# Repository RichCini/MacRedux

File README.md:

# MacRedux

Reimaging of the original Macintosh 128k logic board 820-0086-C. 

## Introduction
This project is a re-implementation of a Macintosh 128k logic board. From this, I hope to
derive the 128k/512k hybrid board. Primarily, I expect these would be used to replace
an original logic board that has been damaged. There are several components that are generally 
"unobtanium" without harvesting from another board. These parts include the six PLDs (of which 
only 2 or 3 may have been decoded per some Google searching), the IWM (disk drive controller), 
the RTC chip (although a clone seems to have been made by someone), three RC dampers, and the 
external floppy connector (a custom 19-pin connector that looks like it used the DB13W3 shell
size). The DB19F was also used on the //gs, Amiga, and NeXT machines, among others. You can 
still occasionally find them on eBay. I purchased 2 just to have them for measurements.

## Project Status
The board has been fully test plotted but has not been sent to manufacturing. I was able to
purchase an original board, so most of the critical measurements have been validated. However,
there still may be minor differences between the original and this version, mostly relating to
the rear connectors, the RJ11 jack, and the pushbutton switches on the side. 

## Versions
* v1.0-001: Initial prototype based on original schematic.

## Known Bugs/Issues
* The board still contains several DRC errors, mostly due to components encroaching on
eachother ("porch violations"). There will likely be permanent encroachments given how
dense the board is in certain areas.

* Certain components (like the push buttons, keyboard connector, and audio jack) 
are being replaced with what I think are current equivalents, so further adjustments could
be needed for those so that they are positioned properly on the planar.

* As of now, the PALs have not been fully decoded. The archive includes a text
file with some notes I've collected on the topic from various places on the Net.

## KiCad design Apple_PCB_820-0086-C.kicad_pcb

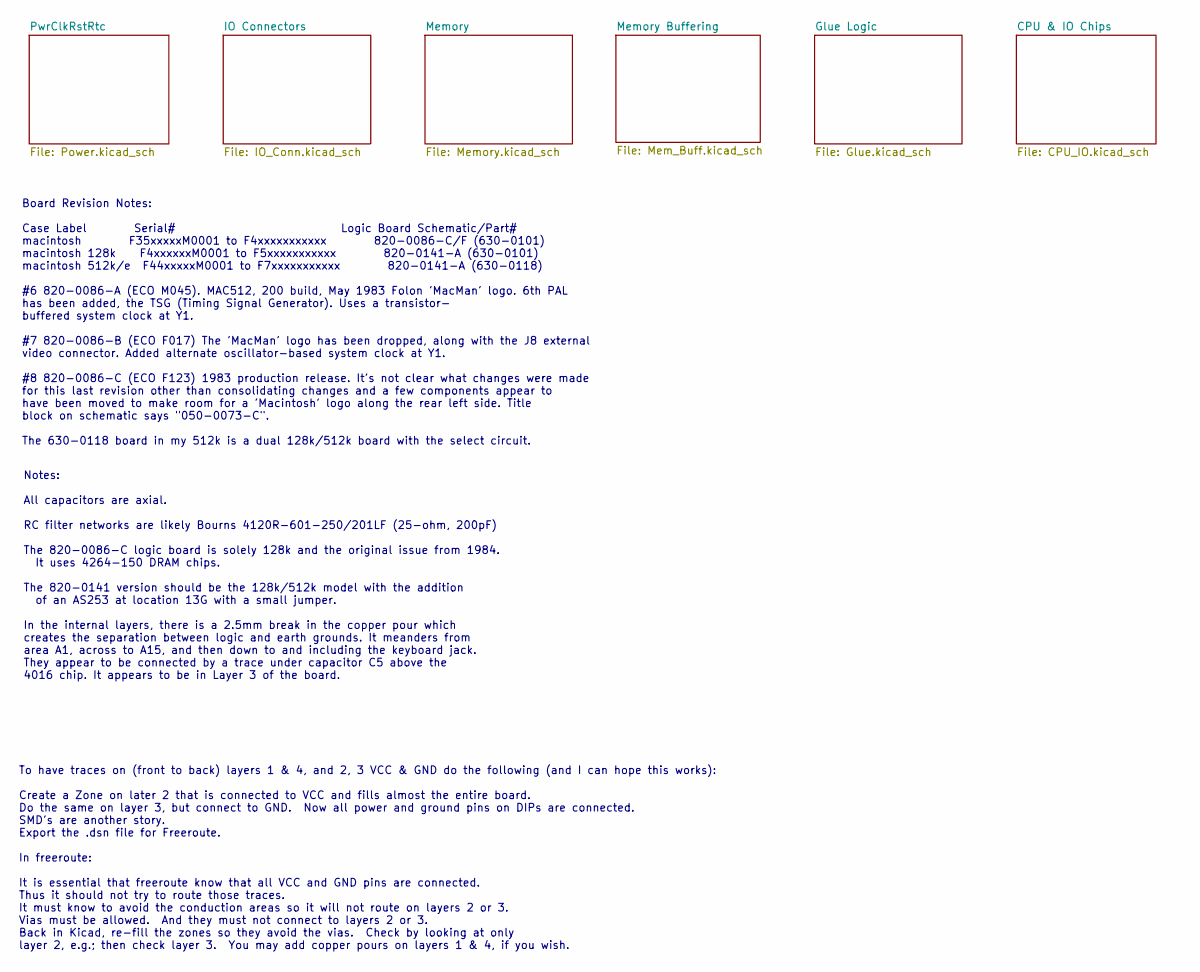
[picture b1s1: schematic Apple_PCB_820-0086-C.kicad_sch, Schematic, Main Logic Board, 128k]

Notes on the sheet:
Board Revision Notes: Case Label Serial# Logic Board Schematic/Part# macintosh F35xxxxxM0001 to F4xxxxxxxxxxx 820-0086-C/F (630-0101) macintosh 128k F4xxxxxxM0001 to F5xxxxxxxxxxx 820-0141-A (630-0101) macintosh 512k/e F44xxxxxM0001 to F7xxxxxxxxxxx 820-0141-A (630-0118) #6 820-0086-A (ECO M045). M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
To have traces on (front to back) layers 1 & 4, and 2, 3 VCC & GND do the following (and I can hope this works): Create a Zone on later 2 that is connected to VCC and fills almost the entire board. Do the same on layer 3, but connect to GND. Now all power and ground pins on DIPs are connected. SMD'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
Notes: All capacitors are axial. RC filter networks are likely Bourns 4120R-601-250/201LF (25-ohm, 200pF) The 820-0086-C logic board is solely 128k and the original issue from 1984. It uses 4264-150 DRAM chips. The 820-0141 version should be the 128k/512k model with the addition of an AS253 at loca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

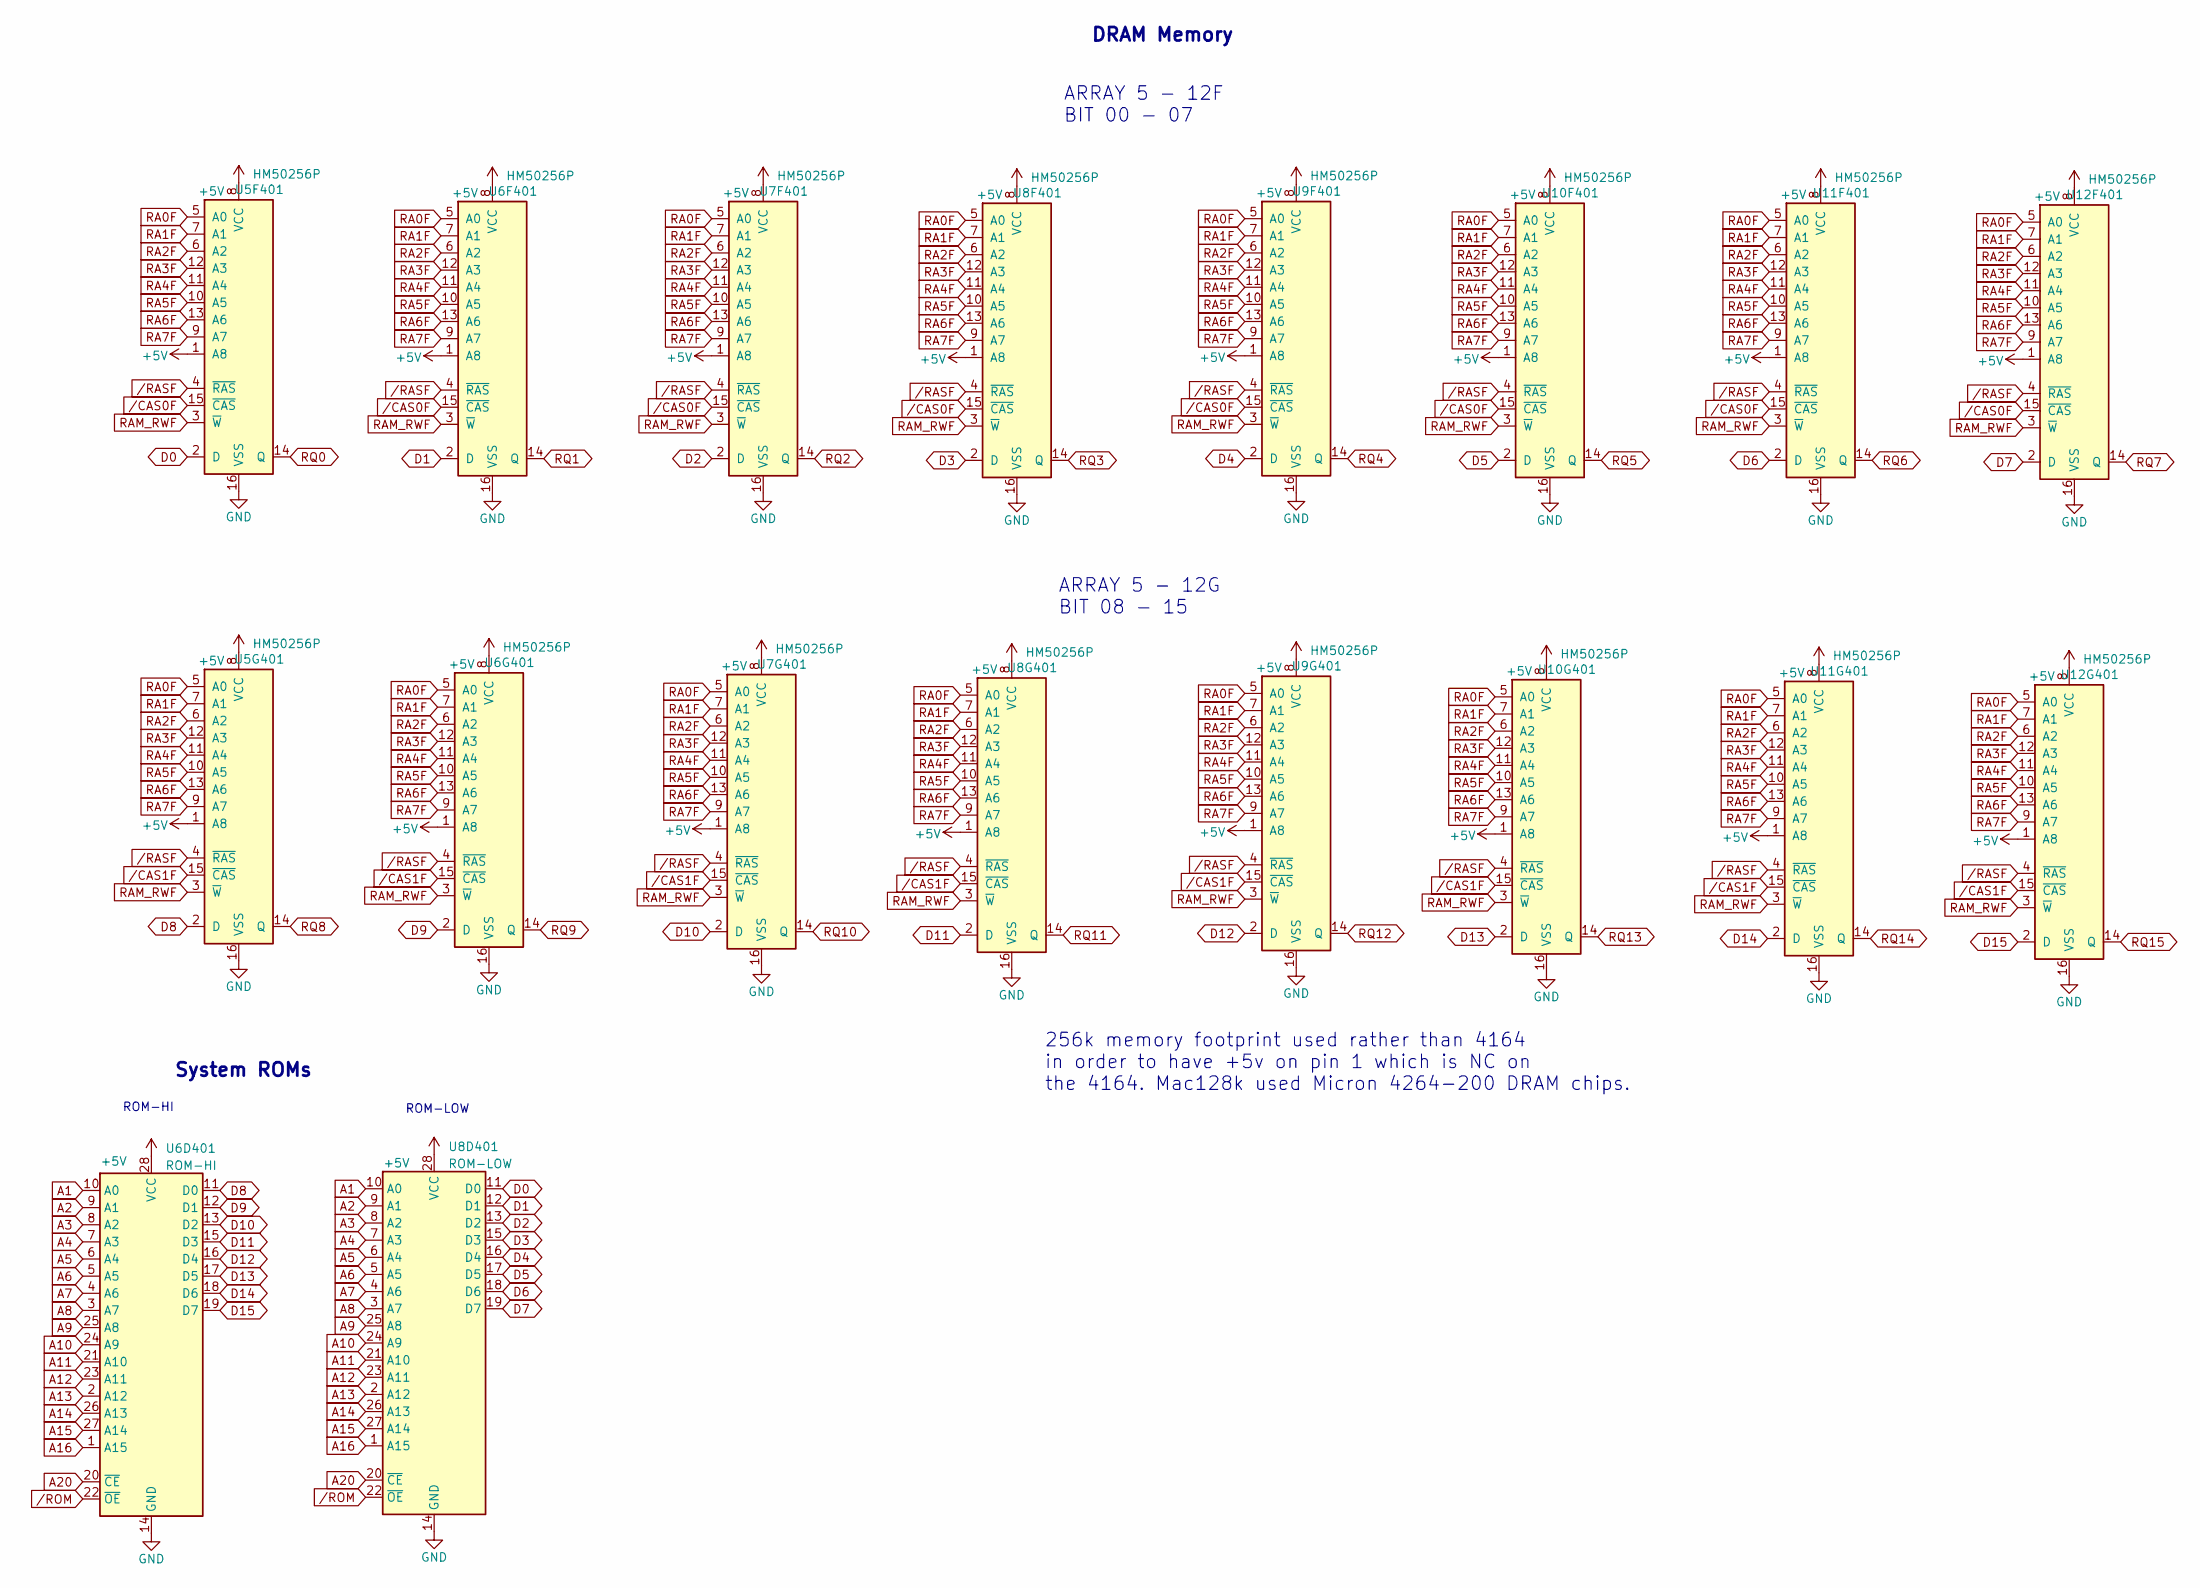
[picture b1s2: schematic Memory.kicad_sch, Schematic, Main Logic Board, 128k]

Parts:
U5F401, U5G401, U6F401, U6G401, U7F401, U7G401, U8F401, U8G401, U9F401, U9G401, U10F401, U10G401, U11F401, U11G401, U12F401, U12G401: HM50256P; DIP-16_W7.62mm_Socket_LongPads
U6D401: ROM-HI; DIP-28_W15.24mm_LongPads
U8D401: ROM-LOW; DIP-28_W15.24mm_LongPads

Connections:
+5V: U5F401.1 (A8), U5F401.8 (VCC), U5G401.1 (A8), U5G401.8 (VCC), U6D401.28 (VCC), U6F401.1 (A8), U6F401.8 (VCC), U6G401.1 (A8), U6G401.8 (VCC), U7F401.1 (A8), U7F401.8 (VCC), U7G401.1 (A8), U7G401.8 (VCC), U8D401.28 (VCC), U8F401.1 (A8), U8F401.8 (VCC), U8G401.1 (A8), U8G401.8 (VCC), U9F401.1 (A8), U9F401.8 (VCC), U9G401.1 (A8), U9G401.8 (VCC), U10F401.1 (A8), U10F401.8 (VCC), U10G401.1 (A8), U10G401.8 (VCC), U11F401.1 (A8), U11F401.8 (VCC), U11G401.1 (A8), U11G401.8 (VCC), U12F401.1 (A8), U12F401.8 (VCC), U12G401.1 (A8), U12G401.8 (VCC); also elsewhere on the board
A1: U6D401.10 (A0), U8D401.10 (A0); also elsewhere on the board
A2: U6D401.9 (A1), U8D401.9 (A1); also elsewhere on the board
A3: U6D401.8 (A2), U8D401.8 (A2); also elsewhere on the board
A4: U6D401.7 (A3), U8D401.7 (A3); also elsewhere on the board
A5: U6D401.6 (A4), U8D401.6 (A4); also elsewhere on the board
A6: U6D401.5 (A5), U8D401.5 (A5); also elsewhere on the board
A7: U6D401.4 (A6), U8D401.4 (A6); also elsewhere on the board
A8: U6D401.3 (A7), U8D401.3 (A7); also elsewhere on the board
A9: U6D401.25 (A8), U8D401.25 (A8); also elsewhere on the board
A10: U6D401.24 (A9), U8D401.24 (A9); also elsewhere on the board
A11: U6D401.21 (A10), U8D401.21 (A10); also elsewhere on the board
A12: U6D401.23 (A11), U8D401.23 (A11); also elsewhere on the board
A13: U6D401.2 (A12), U8D401.2 (A12); also elsewhere on the board
A14: U6D401.26 (A13), U8D401.26 (A13); also elsewhere on the board
A15: U6D401.27 (A14), U8D401.27 (A14); also elsewhere on the board
A16: U6D401.1 (A15), U8D401.1 (A15); also elsewhere on the board
A20: U6D401.20 (~CE), U8D401.20 (~CE); also elsewhere on the board
D0: U5F401.2 (D), U8D401.11 (D0); also elsewhere on the board
D1: U6F401.2 (D), U8D401.12 (D1); also elsewhere on the board
D2: U7F401.2 (D), U8D401.13 (D2); also elsewhere on the board
D3: U8D401.15 (D3), U8F401.2 (D); also elsewhere on the board
D4: U8D401.16 (D4), U9F401.2 (D); also elsewhere on the board
D5: U8D401.17 (D5), U10F401.2 (D); also elsewhere on the board
D6: U8D401.18 (D6), U11F401.2 (D); also elsewhere on the board
D7: U8D401.19 (D7), U12F401.2 (D); also elsewhere on the board
D8: U5G401.2 (D), U6D401.11 (D0); also elsewhere on the board
D9: U6D401.12 (D1), U6G401.2 (D); also elsewhere on the board
D10: U6D401.13 (D2), U7G401.2 (D); also elsewhere on the board
D11: U6D401.15 (D3), U8G401.2 (D); also elsewhere on the board
D12: U6D401.16 (D4), U9G401.2 (D); also elsewhere on the board
D13: U6D401.17 (D5), U10G401.2 (D); also elsewhere on the board
D14: U6D401.18 (D6), U11G401.2 (D); also elsewhere on the board
D15: U6D401.19 (D7), U12G401.2 (D); also elsewhere on the board
GND: U5F401.16 (VSS), U5G401.16 (VSS), U6D401.14 (GND), U6F401.16 (VSS), U6G401.16 (VSS), U7F401.16 (VSS), U7G401.16 (VSS), U8D401.14 (GND), U8F401.16 (VSS), U8G401.16 (VSS), U9F401.16 (VSS), U9G401.16 (VSS), U10F401.16 (VSS), U10G401.16 (VSS), U11F401.16 (VSS), U11G401.16 (VSS), U12F401.16 (VSS), U12G401.16 (VSS); also elsewhere on the board
RA0F: U5F401.5 (A0), U5G401.5 (A0), U6F401.5 (A0), U6G401.5 (A0), U7F401.5 (A0), U7G401.5 (A0), U8F401.5 (A0), U8G401.5 (A0), U9F401.5 (A0), U9G401.5 (A0), U10F401.5 (A0), U10G401.5 (A0), U11F401.5 (A0), U11G401.5 (A0), U12F401.5 (A0), U12G401.5 (A0); also elsewhere on the board
RA1F: U5F401.7 (A1), U5G401.7 (A1), U6F401.7 (A1), U6G401.7 (A1), U7F401.7 (A1), U7G401.7 (A1), U8F401.7 (A1), U8G401.7 (A1), U9F401.7 (A1), U9G401.7 (A1), U10F401.7 (A1), U10G401.7 (A1), U11F401.7 (A1), U11G401.7 (A1), U12F401.7 (A1), U12G401.7 (A1); also elsewhere on the board
RA2F: U5F401.6 (A2), U5G401.6 (A2), U6F401.6 (A2), U6G401.6 (A2), U7F401.6 (A2), U7G401.6 (A2), U8F401.6 (A2), U8G401.6 (A2), U9F401.6 (A2), U9G401.6 (A2), U10F401.6 (A2), U10G401.6 (A2), U11F401.6 (A2), U11G401.6 (A2), U12F401.6 (A2), U12G401.6 (A2); also elsewhere on the board
RA3F: U5F401.12 (A3), U5G401.12 (A3), U6F401.12 (A3), U6G401.12 (A3), U7F401.12 (A3), U7G401.12 (A3), U8F401.12 (A3), U8G401.12 (A3), U9F401.12 (A3), U9G401.12 (A3), U10F401.12 (A3), U10G401.12 (A3), U11F401.12 (A3), U11G401.12 (A3), U12F401.12 (A3), U12G401.12 (A3); also elsewhere on the board
RA4F: U5F401.11 (A4), U5G401.11 (A4), U6F401.11 (A4), U6G401.11 (A4), U7F401.11 (A4), U7G401.11 (A4), U8F401.11 (A4), U8G401.11 (A4), U9F401.11 (A4), U9G401.11 (A4), U10F401.11 (A4), U10G401.11 (A4), U11F401.11 (A4), U11G401.11 (A4), U12F401.11 (A4), U12G401.11 (A4); also elsewhere on the board
RA5F: U5F401.10 (A5), U5G401.10 (A5), U6F401.10 (A5), U6G401.10 (A5), U7F401.10 (A5), U7G401.10 (A5), U8F401.10 (A5), U8G401.10 (A5), U9F401.10 (A5), U9G401.10 (A5), U10F401.10 (A5), U10G401.10 (A5), U11F401.10 (A5), U11G401.10 (A5), U12F401.10 (A5), U12G401.10 (A5); also elsewhere on the board
RA6F: U5F401.13 (A6), U5G401.13 (A6), U6F401.13 (A6), U6G401.13 (A6), U7F401.13 (A6), U7G401.13 (A6), U8F401.13 (A6), U8G401.13 (A6), U9F401.13 (A6), U9G401.13 (A6), U10F401.13 (A6), U10G401.13 (A6), U11F401.13 (A6), U11G401.13 (A6), U12F401.13 (A6), U12G401.13 (A6); also elsewhere on the board
RA7F: U5F401.9 (A7), U5G401.9 (A7), U6F401.9 (A7), U6G401.9 (A7), U7F401.9 (A7), U7G401.9 (A7), U8F401.9 (A7), U8G401.9 (A7), U9F401.9 (A7), U9G401.9 (A7), U10F401.9 (A7), U10G401.9 (A7), U11F401.9 (A7), U11G401.9 (A7), U12F401.9 (A7), U12G401.9 (A7); also elsewhere on the board
RAM_RWF: U5F401.3 (~W), U5G401.3 (~W), U6F401.3 (~W), U6G401.3 (~W), U7F401.3 (~W), U7G401.3 (~W), U8F401.3 (~W), U8G401.3 (~W), U9F401.3 (~W), U9G401.3 (~W), U10F401.3 (~W), U10G401.3 (~W), U11F401.3 (~W), U11G401.3 (~W), U12F401.3 (~W), U12G401.3 (~W); also elsewhere on the board
RQ0: U5F401.14 (Q); also elsewhere on the board
RQ1: U6F401.14 (Q); also elsewhere on the board
RQ2: U7F401.14 (Q); also elsewhere on the board
RQ3: U8F401.14 (Q); also elsewhere on the board
RQ4: U9F401.14 (Q); also elsewhere on the board
RQ5: U10F401.14 (Q); also elsewhere on the board
RQ6: U11F401.14 (Q); also elsewhere on the board
RQ7: U12F401.14 (Q); also elsewhere on the board
RQ8: U5G401.14 (Q); also elsewhere on the board
RQ9: U6G401.14 (Q); also elsewhere on the board
RQ10: U7G401.14 (Q); also elsewhere on the board
RQ11: U8G401.14 (Q); also elsewhere on the board
RQ12: U9G401.14 (Q); also elsewhere on the board
RQ13: U10G401.14 (Q); also elsewhere on the board
RQ14: U11G401.14 (Q); also elsewhere on the board
RQ15: U12G401.14 (Q); also elsewhere on the board
/CAS0F: U5F401.15 (~CAS), U6F401.15 (~CAS), U7F401.15 (~CAS), U8F401.15 (~CAS), U9F401.15 (~CAS), U10F401.15 (~CAS), U11F401.15 (~CAS), U12F401.15 (~CAS); also elsewhere on the board
/CAS1F: U5G401.15 (~CAS), U6G401.15 (~CAS), U7G401.15 (~CAS), U8G401.15 (~CAS), U9G401.15 (~CAS), U10G401.15 (~CAS), U11G401.15 (~CAS), U12G401.15 (~CAS); also elsewhere on the board
/RASF: U5F401.4 (~RAS), U5G401.4 (~RAS), U6F401.4 (~RAS), U6G401.4 (~RAS), U7F401.4 (~RAS), U7G401.4 (~RAS), U8F401.4 (~RAS), U8G401.4 (~RAS), U9F401.4 (~RAS), U9G401.4 (~RAS), U10F401.4 (~RAS), U10G401.4 (~RAS), U11F401.4 (~RAS), U11G401.4 (~RAS), U12F401.4 (~RAS), U12G401.4 (~RAS); also elsewhere on the board
/ROM: U6D401.22 (~OE), U8D401.22 (~OE); also elsewhere on the board

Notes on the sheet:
ARRAY 5 - 12F BIT 00 - 07
ROM-LOW
DRAM Memory
System ROMs
ARRAY 5 - 12G BIT 08 - 15
ROM-HI
256k memory footprint used rather than 4164 in order to have +5v on pin 1 which is NC on the 4164. Mac128k used Micron 4264-200 DRAM chips.

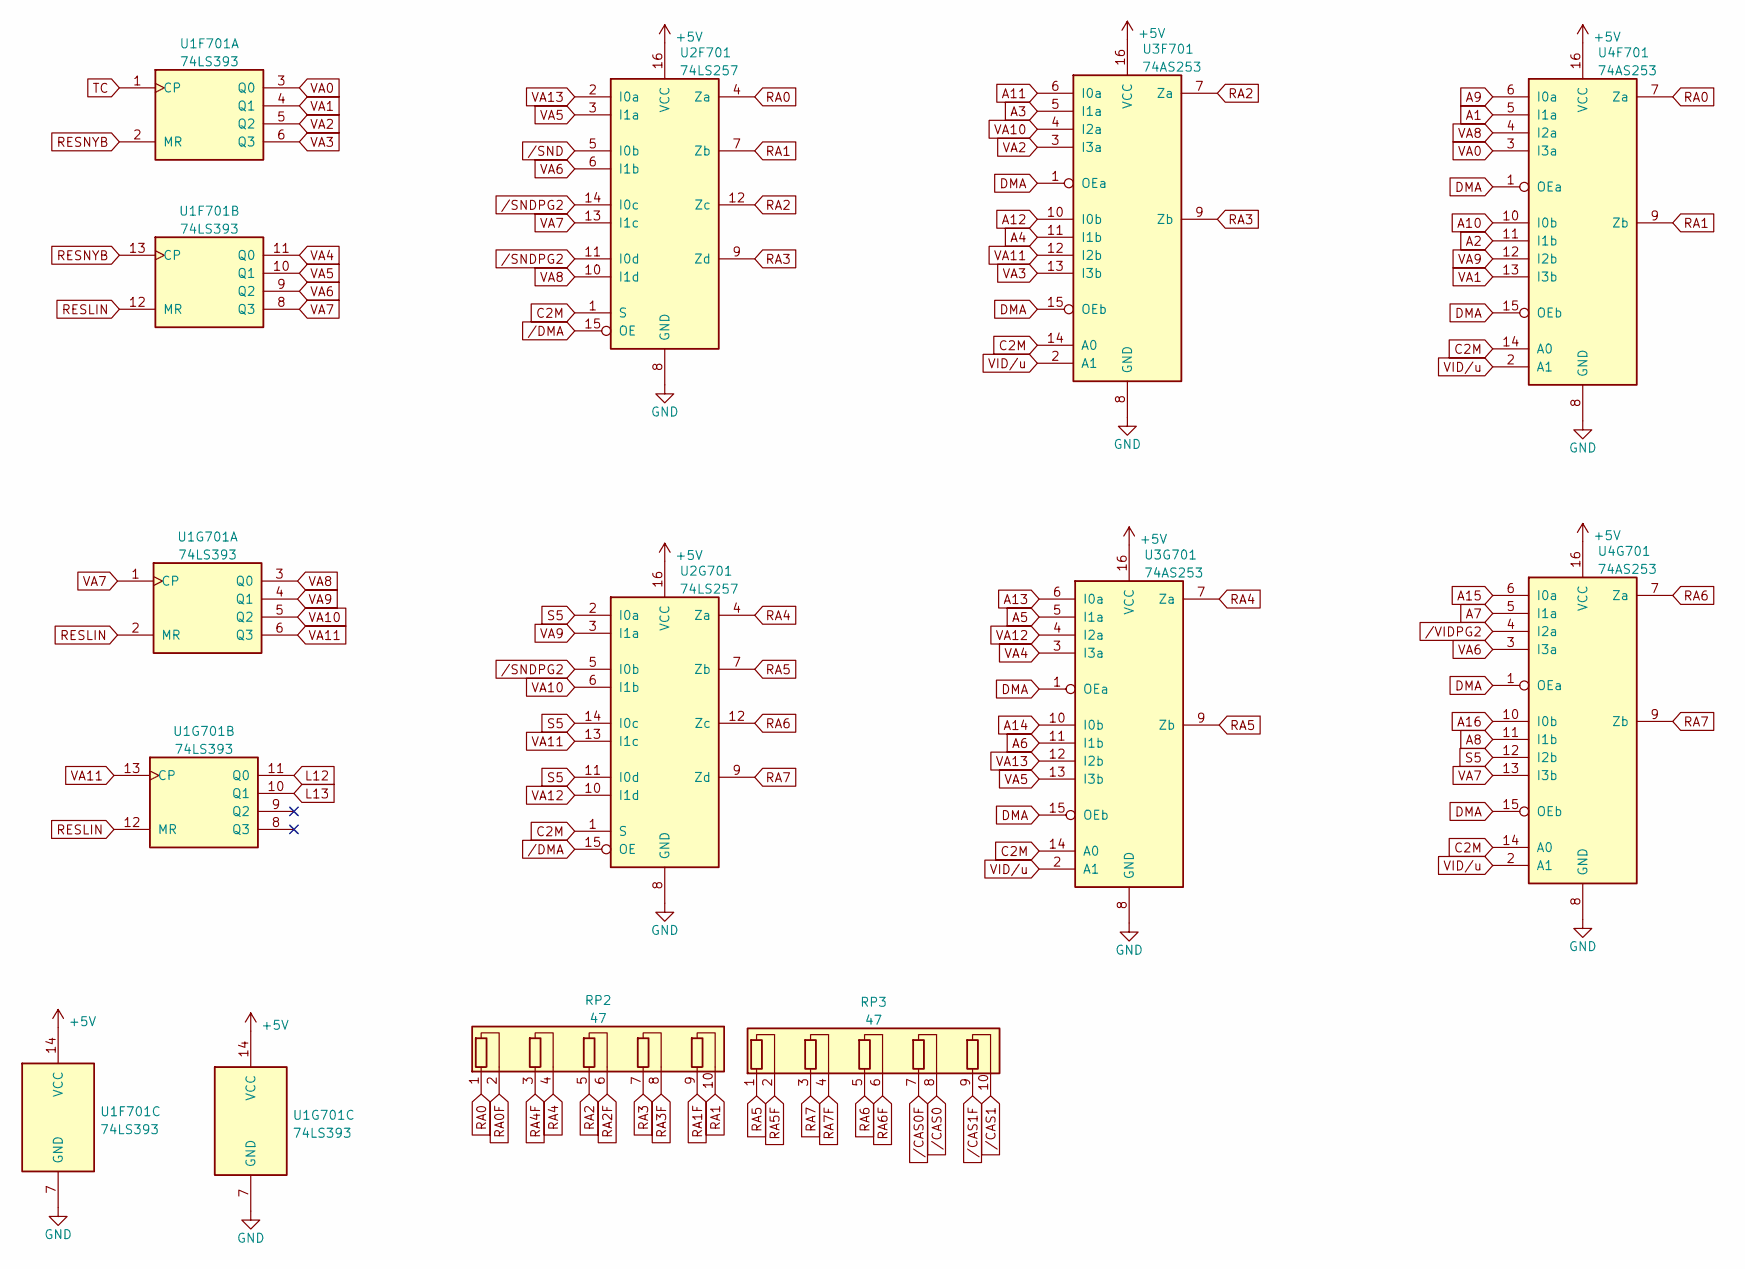
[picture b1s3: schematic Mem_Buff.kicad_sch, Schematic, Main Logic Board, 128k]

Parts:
RP2, RP3: 47; R_Array_SIP10
U1F701, U1G701: 74LS393; DIP-14_W7.62mm_Socket_LongPads
U2F701, U2G701: 74LS257; DIP-16_W7.62mm_Socket_LongPads
U3F701, U3G701, U4F701, U4G701: 74AS253; DIP-16_W7.62mm_Socket_LongPads

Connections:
+5V: U1F701.14 (VCC), U1G701.14 (VCC), U2F701.16 (VCC), U2G701.16 (VCC), U3F701.16 (VCC), U3G701.16 (VCC), U4F701.16 (VCC), U4G701.16 (VCC); also elsewhere on the board
A1: U4F701.5 (I1a); also elsewhere on the board
A2: U4F701.11 (I1b); also elsewhere on the board
A3: U3F701.5 (I1a); also elsewhere on the board
A4: U3F701.11 (I1b); also elsewhere on the board
A5: U3G701.5 (I1a); also elsewhere on the board
A6: U3G701.11 (I1b); also elsewhere on the board
A7: U4G701.5 (I1a); also elsewhere on the board
A8: U4G701.11 (I1b); also elsewhere on the board
A9: U4F701.6 (I0a); also elsewhere on the board
A10: U4F701.10 (I0b); also elsewhere on the board
A11: U3F701.6 (I0a); also elsewhere on the board
A12: U3F701.10 (I0b); also elsewhere on the board
A13: U3G701.6 (I0a); also elsewhere on the board
A14: U3G701.10 (I0b); also elsewhere on the board
A15: U4G701.6 (I0a); also elsewhere on the board
A16: U4G701.10 (I0b); also elsewhere on the board
C2M: U2F701.1 (S), U2G701.1 (S), U3F701.14 (A0), U3G701.14 (A0), U4F701.14 (A0), U4G701.14 (A0); also elsewhere on the board
DMA: U3F701.1 (OEa), U3F701.15 (OEb), U3G701.1 (OEa), U3G701.15 (OEb), U4F701.1 (OEa), U4F701.15 (OEb), U4G701.1 (OEa), U4G701.15 (OEb); also elsewhere on the board
GND: U1F701.7 (GND), U1G701.7 (GND), U2F701.8 (GND), U2G701.8 (GND), U3F701.8 (GND), U3G701.8 (GND), U4F701.8 (GND), U4G701.8 (GND); also elsewhere on the board
L12: U1G701.11 (Q0); also elsewhere on the board
L13: U1G701.10 (Q1); also elsewhere on the board
RA0: RP2.1 (R1.1), U2F701.4 (Za), U4F701.7 (Za)
RA0F: RP2.2 (R1.2); also elsewhere on the board
RA1: RP2.10 (R5.2), U2F701.7 (Zb), U4F701.9 (Zb)
RA1F: RP2.9 (R5.1); also elsewhere on the board
RA2: RP2.5 (R3.1), U2F701.12 (Zc), U3F701.7 (Za)
RA2F: RP2.6 (R3.2); also elsewhere on the board
RA3: RP2.7 (R4.1), U2F701.9 (Zd), U3F701.9 (Zb)
RA3F: RP2.8 (R4.2); also elsewhere on the board
RA4: RP2.4 (R2.2), U2G701.4 (Za), U3G701.7 (Za)
RA4F: RP2.3 (R2.1); also elsewhere on the board
RA5: RP3.1 (R1.1), U2G701.7 (Zb), U3G701.9 (Zb)
RA5F: RP3.2 (R1.2); also elsewhere on the board
RA6: RP3.5 (R3.1), U2G701.12 (Zc), U4G701.7 (Za)
RA6F: RP3.6 (R3.2); also elsewhere on the board
RA7: RP3.3 (R2.1), U2G701.9 (Zd), U4G701.9 (Zb)
RA7F: RP3.4 (R2.2); also elsewhere on the board
RESLIN: U1F701.12 (MR), U1G701.2 (MR), U1G701.12 (MR); also elsewhere on the board
RESNYB: U1F701.2 (MR), U1F701.13 (CP); also elsewhere on the board
S5: U2G701.2 (I0a), U2G701.11 (I0d), U2G701.14 (I0c), U4G701.12 (I2b); also elsewhere on the board
TC: U1F701.1 (CP); also elsewhere on the board
VA0: U1F701.3 (Q0), U4F701.3 (I3a); also elsewhere on the board
VA1: U1F701.4 (Q1), U4F701.13 (I3b); also elsewhere on the board
VA2: U1F701.5 (Q2), U3F701.3 (I3a); also elsewhere on the board
VA3: U1F701.6 (Q3), U3F701.13 (I3b); also elsewhere on the board
VA4: U1F701.11 (Q0), U3G701.3 (I3a)
VA5: U1F701.10 (Q1), U2F701.3 (I1a), U3G701.13 (I3b)
VA6: U1F701.9 (Q2), U2F701.6 (I1b), U4G701.3 (I3a); also elsewhere on the board
VA7: U1F701.8 (Q3), U1G701.1 (CP), U2F701.13 (I1c), U4G701.13 (I3b); also elsewhere on the board
VA8: U1G701.3 (Q0), U2F701.10 (I1d), U4F701.4 (I2a); also elsewhere on the board
VA9: U1G701.4 (Q1), U2G701.3 (I1a), U4F701.12 (I2b); also elsewhere on the board
VA10: U1G701.5 (Q2), U2G701.6 (I1b), U3F701.4 (I2a); also elsewhere on the board
VA11: U1G701.6 (Q3), U1G701.13 (CP), U2G701.13 (I1c), U3F701.12 (I2b); also elsewhere on the board
VA12: U2G701.10 (I1d), U3G701.4 (I2a); also elsewhere on the board
VA13: U2F701.2 (I0a), U3G701.12 (I2b); also elsewhere on the board
VID/u: U3F701.2 (A1), U3G701.2 (A1), U4F701.2 (A1), U4G701.2 (A1); also elsewhere on the board
/CAS0: RP3.8 (R4.2); also elsewhere on the board
/CAS0F: RP3.7 (R4.1); also elsewhere on the board
/CAS1: RP3.10 (R5.2); also elsewhere on the board
/CAS1F: RP3.9 (R5.1); also elsewhere on the board
/DMA: U2F701.15 (OE), U2G701.15 (OE); also elsewhere on the board
/SND: U2F701.5 (I0b); also elsewhere on the board
/SNDPG2: U2F701.11 (I0d), U2F701.14 (I0c), U2G701.5 (I0b); also elsewhere on the board
/VIDPG2: U4G701.4 (I2a); also elsewhere on the board

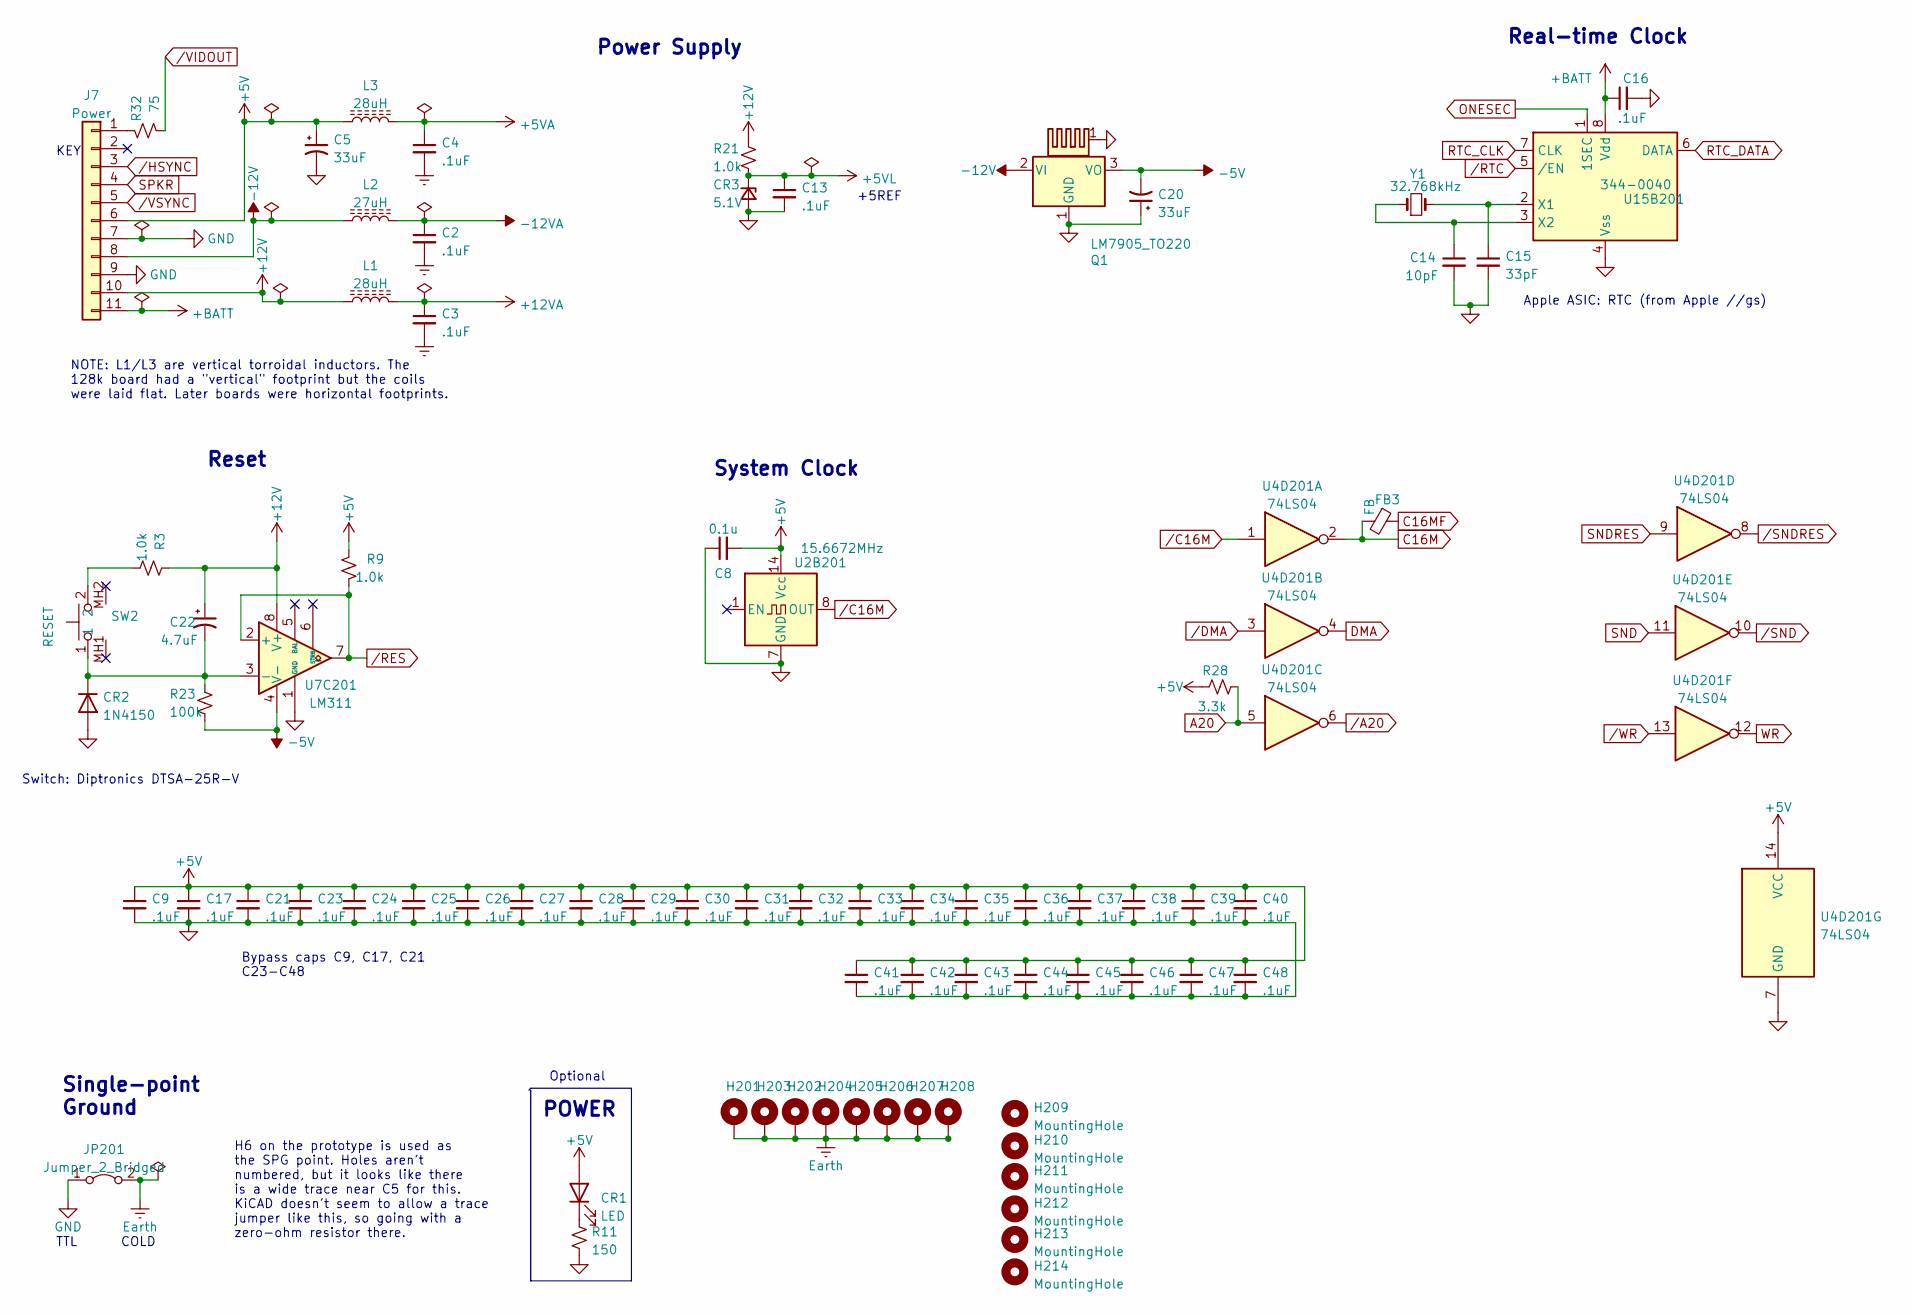
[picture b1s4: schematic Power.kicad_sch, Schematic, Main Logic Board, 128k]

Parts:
C2, C3, C4, C9, C13, C16, C17, C23, C24, C25, C26, C27, C28, C29, C30, C31, C32, C33, C34, C35, C36, C37, C38, C39, C40, C41, C42, C43, C44, C45, C46, C47, C48: .1uF; C_Axial_L3.8mm_D2.6mm_P7.50mm_Horizontal
C5, C20: 33uF; CP_Axial_L11.0mm_D6.0mm_P18.00mm_Horizontal
C8: 0.1u; C_Axial_L3.8mm_D2.6mm_P7.50mm_Horizontal
C14: 10pF; C_Axial_L3.8mm_D2.6mm_P7.50mm_Horizontal
C15: 33pF; C_Axial_L3.8mm_D2.6mm_P7.50mm_Horizontal
C21: .1uF; C_Axial_L5.1mm_D3.1mm_P10.00mm_Horizontal
C22: 4.7uF; CP_Axial_L11.0mm_D5.0mm_P18.00mm_Horizontal
CR1: LED; LED_D5.0mm
CR2: 1N4150; D_DO-35_SOD27_P7.62mm_Horizontal
CR3: 5.1V; D_DO-35_SOD27_P7.62mm_Horizontal
FB3: FB; L_Axial_L7.0mm_D3.3mm_P10.16mm_Horizontal_Fastron_MICC
H201, H202, H203, H204, H205, H206, H207, H208: MountingHole_Pad; MountingHole_2.7mm_M2.5_Pad
H209, H210, H211, H212, H213, H214: MountingHole; MountingHole_2.7mm_M2.5
J7: Power; Molex_KK-396_A-41791-0011_1x11_P3.96mm_Vertical
JP201: Jumper_2_Bridged; TestPoint_Bridge_Pitch5.08mm_Drill0.7mm
L1, L3: 28uH; L_Toroid_Vertical_L14.0mm_W5.6mm_P5.30mm_Bourns_5700
L2: 27uH; L_Axial_L7.0mm_D3.3mm_P10.16mm_Horizontal_Fastron_MICC
Q1: LM7905_TO220; TO-220-3_Horizontal_TabDown_HS
R3, R9, R21: 1.0k; R_Axial_DIN0207_L6.3mm_D2.5mm_P7.62mm_Horizontal
R11: 150; R_Axial_DIN0207_L6.3mm_D2.5mm_P7.62mm_Horizontal
R23: 100k; R_Axial_DIN0207_L6.3mm_D2.5mm_P7.62mm_Horizontal
R28: 3.3k; R_Axial_DIN0207_L6.3mm_D2.5mm_P7.62mm_Horizontal
R32: 75; R_Axial_DIN0207_L6.3mm_D2.5mm_P7.62mm_Horizontal
SW2: RESET; TL1100CF160Q
U2B201: 15.6672MHz; Oscillator_DIP-14
U4D201: 74LS04; DIP-14_W7.62mm_Socket_LongPads
U7C201: LM311; DIP-8_W7.62mm_Socket_LongPads
U15B201: 344-0040; DIP-8_W7.62mm_Socket_LongPads
Y1: 32.768kHz; Crystal_C26-LF_D2.1mm_L6.5mm_Horizontal

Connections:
+5V: C5.1, C8.2, C9.1, C17.1, C21.1, C23.1, C24.1, C25.1, C26.1, C27.1, C28.1, C29.1, C30.1, C31.1, C32.1, C33.1, C34.1, C35.1, C36.1, C37.1, C38.1, C39.1, C40.1, C41.1, C42.1, C43.1, C44.1, C45.1, C46.1, C47.1, C48.1, CR1.2 (A), J7.6, L3.1, R9.1, R28.1, U2B201.14 (Vcc), U4D201.14 (VCC); also elsewhere on the board
+5VA: C4.1, L3.2; also elsewhere on the board
+5VL: C13.1, CR3.1 (K), R21.2; also elsewhere on the board
+12V: C22.1, J7.10, L1.1, R3.1, R21.1, U7C201.8 (V+); also elsewhere on the board
+12VA: C3.1, L1.2; also elsewhere on the board
+BATT: C16.1, J7.11, U15B201.8 (Vdd)
-5V: C20.2, Q1.3 (VO), R23.2, U7C201.4 (V-); also elsewhere on the board
-12V: J7.8, L2.1, Q1.2 (VI); also elsewhere on the board
-12VA: C2.1, L2.2; also elsewhere on the board
A20: R28.2, U4D201.5; also elsewhere on the board
C16M: FB3.2, U4D201.2; also elsewhere on the board
C16MF: FB3.1; also elsewhere on the board
DMA: U4D201.4; also elsewhere on the board
Earth: C2.2, C3.2, C4.2, H201.1, H202.1, H203.1, H204.1, H205.1, H206.1, H207.1, H208.1, JP201.2 (B); also elsewhere on the board
GND: C5.2, C8.1, C9.2, C13.2, C14.2, C15.2, C16.2, C17.2, C20.1, C21.2, C23.2, C24.2, C25.2, C26.2, C27.2, C28.2, C29.2, C30.2, C31.2, C32.2, C33.2, C34.2, C35.2, C36.2, C37.2, C38.2, C39.2, C40.2, C41.2, C42.2, C43.2, C44.2, C45.2, C46.2, C47.2, C48.2, CR2.2 (A), CR3.2 (A), J7.7, J7.9, JP201.1 (A), Q1.1 (GND), R11.2, U2B201.7 (GND), U4D201.7 (GND), U7C201.1 (GND), U15B201.4 (Vss); also elsewhere on the board
unnamed: C14.1, U15B201.3 (X2), Y1.1
unnamed: C15.1, U15B201.2 (X1), Y1.2
unnamed: C22.2, CR2.1 (K), R23.1, SW2.1, U7C201.3 (-)
unnamed: CR1.1 (K), R11.1
unnamed: J7.1, R32.1
unnamed: R3.2, SW2.2
ONESEC: U15B201.1 (1SEC); also elsewhere on the board
RTC_CLK: U15B201.7 (CLK); also elsewhere on the board
RTC_DATA: U15B201.6 (DATA); also elsewhere on the board
SND: U4D201.11; also elsewhere on the board
SNDRES: U4D201.9; also elsewhere on the board
SPKR: J7.4; also elsewhere on the board
WR: U4D201.12; also elsewhere on the board
/A20: U4D201.6; also elsewhere on the board
/C16M: U2B201.8 (OUT), U4D201.1
/DMA: U4D201.3; also elsewhere on the board
/HSYNC: J7.3; also elsewhere on the board
/RES: R9.2, U7C201.2 (+), U7C201.7; also elsewhere on the board
/RTC: U15B201.5 (/EN); also elsewhere on the board
/SND: U4D201.10; also elsewhere on the board
/SNDRES: U4D201.8; also elsewhere on the board
/VIDOUT: R32.2; also elsewhere on the board
/VSYNC: J7.5; also elsewhere on the board
/WR: U4D201.13; also elsewhere on the board

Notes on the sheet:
Apple ASIC: RTC (from Apple //gs)
Bypass caps C9, C17, C21 C23-C48
Power Supply
POWER
+5REF
Optional
COLD
Real-time Clock
NOTE: L1/L3 are vertical torroidal inductors. The 128k board had a "vertical" footprint but the coils were laid flat. Later boards were horizontal footprints.
Single-point Ground
KEY
H6 on the prototype is used as the SPG point. Holes aren't numbered, but it looks like there is a wide trace near C5 for this. KiCAD doesn't seem to allow a trace jumper like this, so going with a zero-ohm resistor there.
TTL
Reset
Switch: Diptronics DTSA-25R-V
System Clock

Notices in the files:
Apple_PCB_820-0086-C.kicad_pcb:
APPLE COMPUTER (C) 1983
(C) 1983 APPLE COMPUTER
(c) 1983  630-0101
